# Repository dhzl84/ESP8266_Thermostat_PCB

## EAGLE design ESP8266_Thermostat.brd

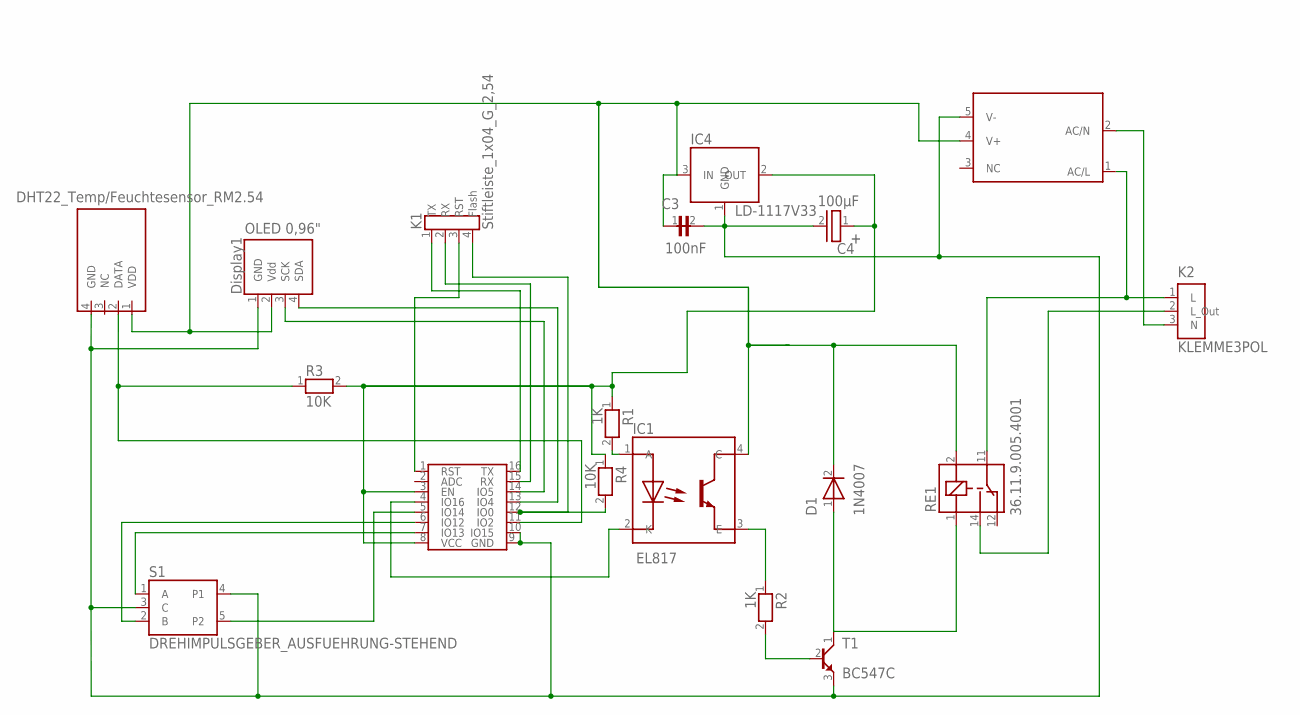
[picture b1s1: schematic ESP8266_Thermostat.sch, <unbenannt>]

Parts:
C3: 100nF; 3X5R5,08_15
C4: 100µF; D5R2,54_ELKO_16
D1: 1N4007; D_RM12,7_DM3_4
Display1: OLED 0,96"; OLED_0,96"_9
IC1: EL817; DIL4_0
IC2: ESP8266-07; ESP8266-7_6
IC3: DHT22_Temp/Feuchtesensor_RM2.54; DHT_RM2.54_8
IC4: LD-1117V33; TO220_13
IC5: IRM-03-5; IRM-03-5_17
K1: Stiftleiste_1x04_G_2,54; Stiftleiste_1x04_G_2,54_11
K2: KLEMME3POL; KLEMME3_14
R1: 1K; 0204_MET_1
R2: 1K; 0204_MET_2
R3: 10K; 0204_10
R4: 10K; 0204_12
RE1: 36.11.9.005.4001; Finder_36.11-4001_5
S1: DREHIMPULSGEBER_AUSFUEHRUNG-STEHEND; DREHIMPULSGEBER_STEHEND_7
T1: BC547C; TO92_3

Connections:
1: IC1.3 (E), R2.1
2: R2.2, T1.2 (B)
+3.3V: C4.1 (+), IC2.3 (EN), IC2.8 (VCC), IC4.2 (OUT), R1.1, R3.2, R4.1
+5V: C3.1, D1.2 (K), Display1.2 (Vdd), IC1.4 (C), IC3.1 (VDD), IC4.3 (IN), IC5.4 (V+), RE1.2 (A2)
A: D1.1 (A), RE1.1 (A1), T1.1 (C)
AC/L: IC5.1 (AC/L), K2.1 (L), RE1.11 (14)
AC/N: IC5.2 (AC/N), K2.3 (N)
DHT22_DATA: IC2.11 (IO2), IC3.2 (DATA), R3.1
Flash: IC2.12 (IO0), K1.4 (Flash), R4.2
GND: C3.2, C4.2 (-), Display1.1 (GND), IC2.9 (GND), IC2.10 (IO15), IC3.4 (GND), IC4.1 (GND), IC5.5 (V-), S1.3 (C), S1.4 (P1), T1.3 (E)
OLED_SCK: Display1.3 (SCK), IC2.14 (IO5)
OLED_SDA: Display1.4 (SDA), IC2.13 (IO4)
RST: IC2.1 (RST), K1.3 (RST)
RX: IC2.15 (RX), K1.2 (RX)
RotEnc_A: IC2.7 (IO13), S1.1 (A)
RotEnc_B: IC2.6 (IO12), S1.2 (B)
RotEnc_P2: IC2.5 (IO14), S1.5 (P2)
Sig$7: IC1.1 (A), R1.2
Sig$20: K2.2 (L_Out), RE1.14 (12)
Switch_OC_Relais: IC1.2 (K), IC2.4 (IO16)
TX: IC2.16 (TX), K1.1 (TX)

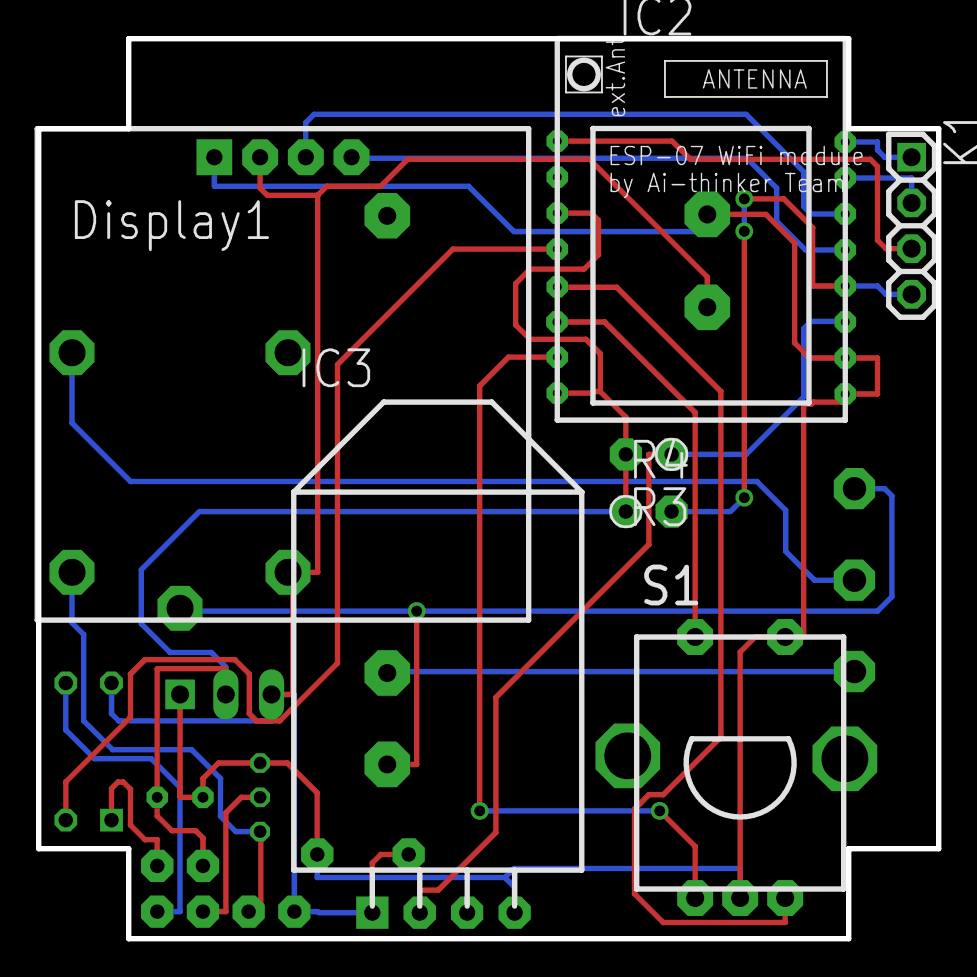
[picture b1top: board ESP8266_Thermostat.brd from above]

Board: 2 copper layers, 50.0 x 50.0 mm, 18 parts (0 on the bottom side), 21 nets.

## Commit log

2017-12-11 PCB V2
2018-11-11 add fuse and fix ESP housing
